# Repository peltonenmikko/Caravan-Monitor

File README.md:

# Caravan-Monitor
For monitoring caravan stuff

This is an STM32 powered monitoring station for different kinds of sensors made with caravans in mind.
It is powered by 12v car batteries. All other are off the board and connected with wires.

It shows the values on a cheap I²C OLED display and there is one button to browse the values.

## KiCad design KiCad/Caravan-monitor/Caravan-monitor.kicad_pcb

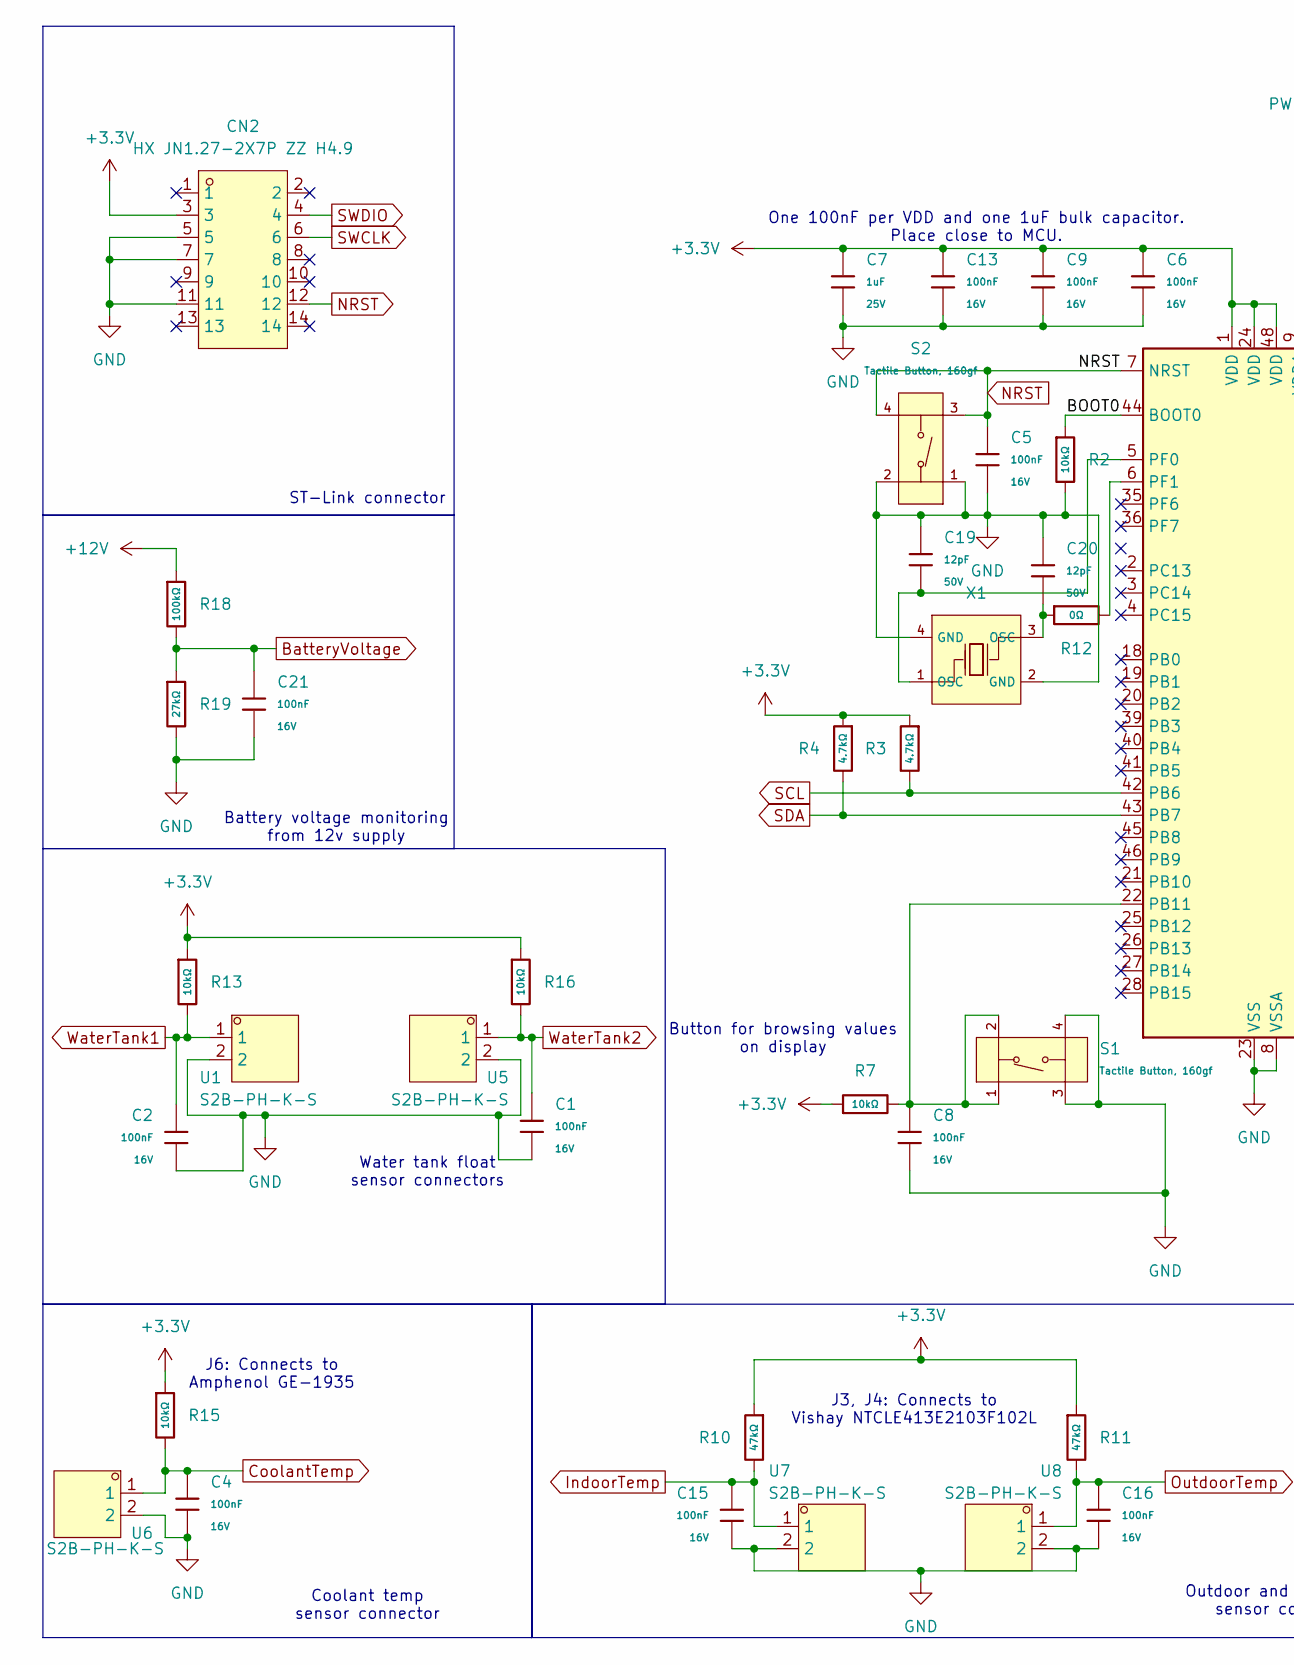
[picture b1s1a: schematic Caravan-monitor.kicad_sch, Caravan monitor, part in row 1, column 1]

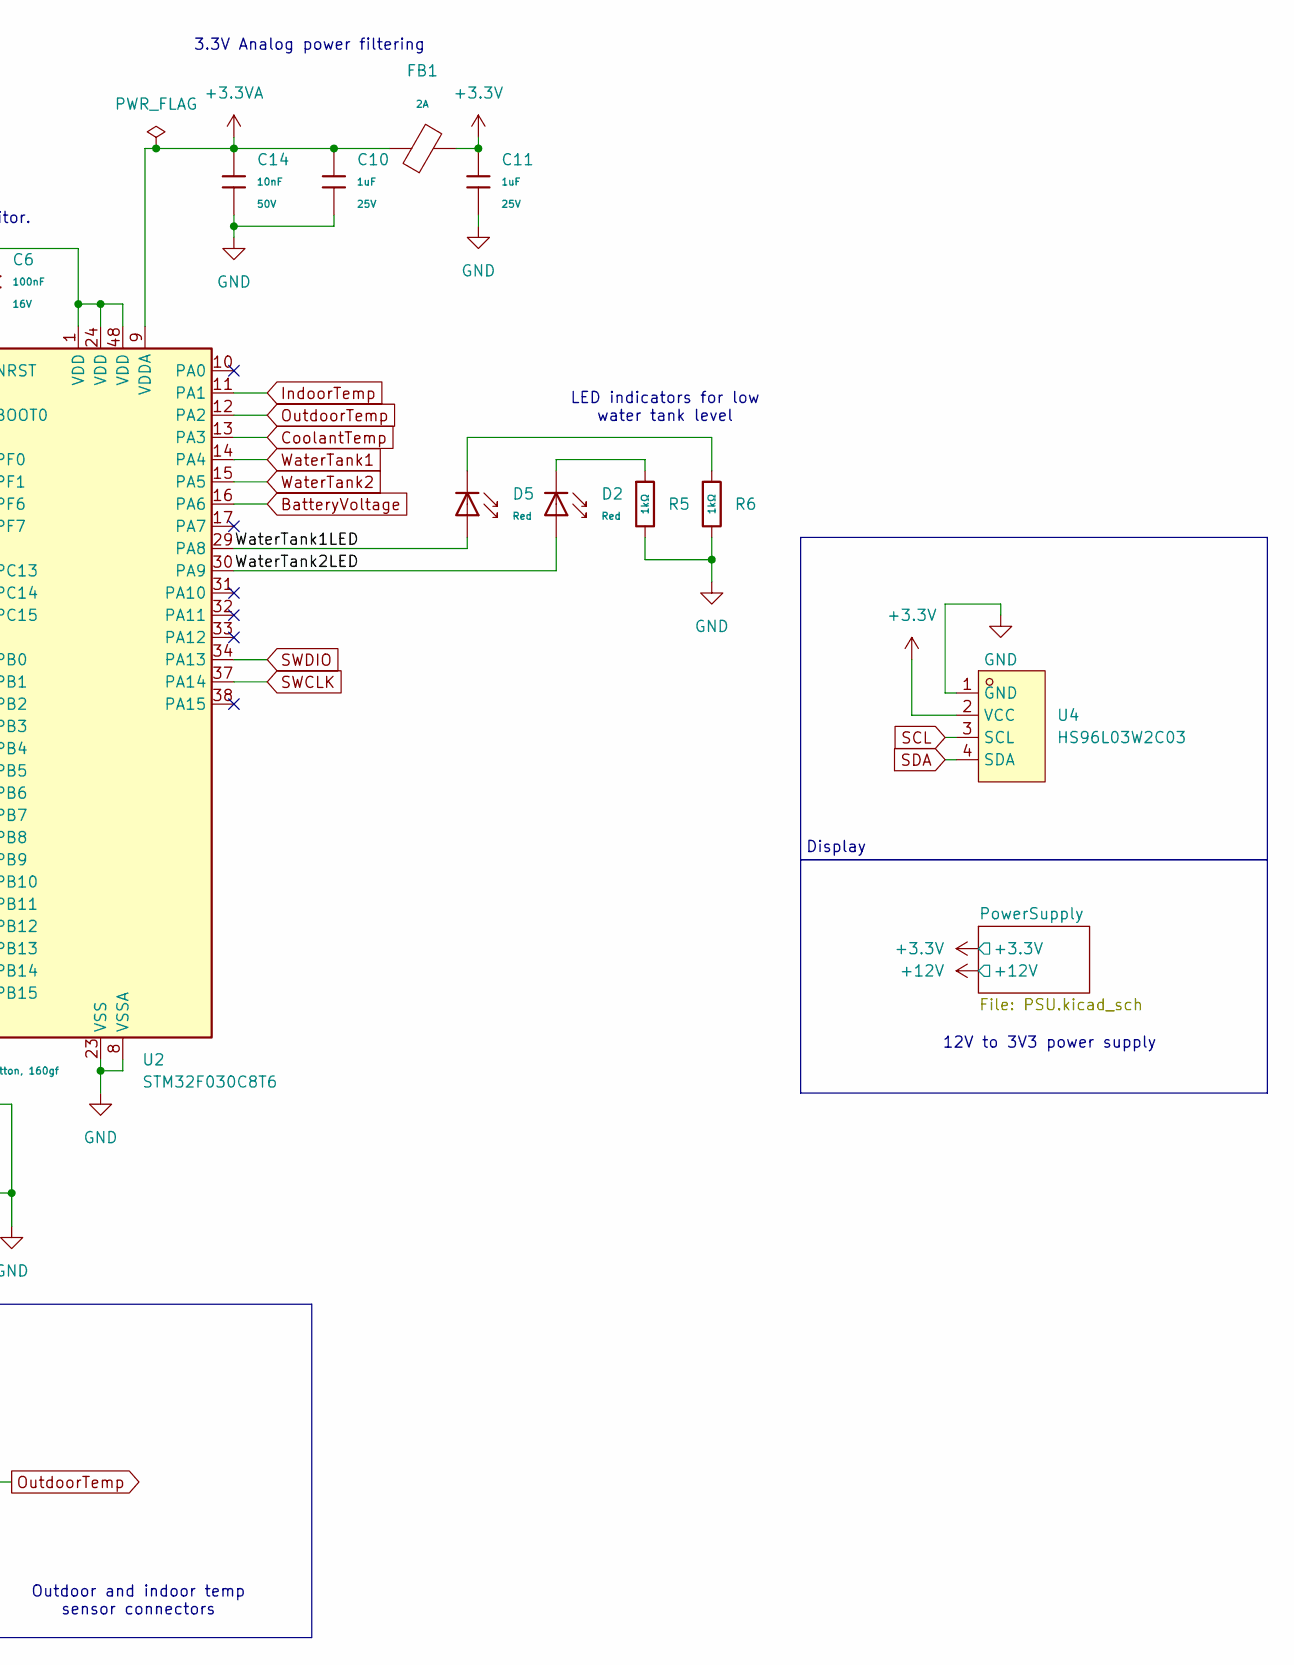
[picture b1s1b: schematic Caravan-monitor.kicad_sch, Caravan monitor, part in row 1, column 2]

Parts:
C1, C2, C4, C5, C6, C8, C9, C13, C15, C16, C21: 100nF; C_0402; Voltage Rated 16V; Tolerance ±10%; Part CL05B104KO5NNNC; LCSC C1525
C7, C10, C11: 1uF; C_0402; Voltage Rated 25V; Tolerance ±10%; Part CL05A105KA5NQNC; LCSC C52923
C14: 10nF; C_0402; Voltage Rated 50V; Tolerance ±10%; Part CL05B103KB5NNNC; LCSC C15195
C19, C20: 12pF; C_0402; Voltage Rated 50V; Tolerance ±5%; Part 0402CG120J500NT; LCSC C1547
CN2: HX JN1.27-2X7P ZZ H4.9; IDC-TH_14P-P1.27_C42455940; MPN HX JN1.27-2x7P ZZ H4.9; LCSC Part C42455940
D2, D5: Red; D_0603; Part KT-0603R; LCSC C2286
FB1: FB_0603; Current Rating 2A; Tolerance ±25%; Part BLM18PG121SN1D; LCSC C14709
R2, R7, R13, R15, R16: 10kΩ; R_0402; Overload Voltage (Max) 50V; Tolerance ±1%; Part 0402WGF1002TCE; LCSC C25744
R3, R4: 4.7kΩ; R_0402; Overload Voltage (Max) 50V; Tolerance ±1%; Part 0402WGF4701TCE; LCSC C25900
R5, R6: 1kΩ; R_0402; Overload Voltage (Max) 50V; Tolerance ±1%; Part 0402WGF1001TCE; LCSC C11702
R10, R11: 47kΩ; R_0402; Overload Voltage (Max) 50V; Tolerance ±1%; Part 0402WGF4702TCE; LCSC C25792
R12: 0Ω; R_0402; Overload Voltage (Max) 50V; Tolerance ±1%; Part 0402WGF0000TCE; LCSC C17168
R18: 100kΩ; R_0402; Overload Voltage (Max) 50V; Tolerance ±1%; Part 0402WGF1003TCE; LCSC C25741
R19: 27kΩ; R_0402; Overload Voltage (Max) 50V; Tolerance ±1%; Part 0402WGF2702TCE; LCSC C25771
S1, S2: Tactile Button, 160gf; SW-SMD_4P-L5.1-W5.1-P3.70-LS6.5-TL-2; Voltage Rating (Dc) 12V; Part TS-1187A-B-A-B; LCSC C318884
U1, U5, U6, U7, U8: S2B-PH-K-S; CONN-TH_S2B-PH-K-S-LF-SN; MPN S2B-PH-K-S(LF)(SN); LCSC Part C173752
U2: STM32F030C8T6; LQFP-48_7x7mm_P0.5mm; Operating Voltage Range 2.4V~3.6V; Low Voltage Detection T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 2.4V~3.6V; Part STM32F030C8T6; LCSC C23922
U4: HS96L03W2C03; OLED-TH_L27.8-W27.2-P2.54_C9900033791; MPN HS96L03W2C03; LCSC Part C5248080
X1: X322516MLB4SI; OSC-SMD_4P-L3.2-W2.5-BL; Frequency Tolerance ±10ppm; Part X322516MLB4SI; LCSC C13738

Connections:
+3.3V: C6.1, C7.1, C9.1, C11.1, C13.1, CN2.3, FB1.2, R3.1, R4.1, R7.1, R10.1, R11.1, R13.1, R15.1, R16.1, U2.1 (VDD), U2.24 (VDD), U2.48 (VDD), U4.2 (VCC); also elsewhere on the board
+3.3VA: C10.1, C14.1, FB1.1, U2.9 (VDDA)
+12V: R18.1; also elsewhere on the board
/BOOT0: R2.1, U2.44 (BOOT0)
/WaterTank1LED: D5.2, U2.29 (PA8)
/WaterTank2LED: D2.2, U2.30 (PA9)
BatteryVoltage: C21.1, R18.2, R19.1, U2.16 (PA6)
CoolantTemp: C4.1, R15.2, U2.13 (PA3), U6.1
GND: C1.2, C2.2, C4.2, C5.2, C6.2, C7.2, C8.2, C9.2, C10.2, C11.2, C13.2, C14.2, C15.2, C16.2, C19.1, C20.1, C21.2, CN2.5, CN2.7, CN2.11, R2.2, R5.2, R6.2, R19.2, S1.3 (C), S1.4 (D), S2.1 (A), S2.2 (B), U1.2, U2.8 (VSSA), U2.23 (VSS), U2.47 (VSS), U4.1 (GND), U5.2, U6.2, U7.2, U8.2, X1.2 (GND), X1.4 (GND); also elsewhere on the board
IndoorTemp: C15.1, R10.2, U2.11 (PA1), U7.1
NRST: C5.1, CN2.12, S2.3 (C), S2.4 (D), U2.7 (NRST)
unnamed: C20.2, R12.1, X1.3 (OSC)
unnamed: D2.1, R5.1
unnamed: D5.1, R6.1
unnamed: C8.1, R7.2, S1.1 (A), S1.2 (B), U2.22 (PB11)
unnamed: C19.2, U2.5 (PF0), X1.1 (OSC)
unnamed: R12.2, U2.6 (PF1)
OutdoorTemp: C16.1, R11.2, U2.12 (PA2), U8.1
SCL: R3.2, U2.42 (PB6), U4.3 (SCL)
SDA: R4.2, U2.43 (PB7), U4.4 (SDA)
SWCLK: CN2.6, U2.37 (PA14)
SWDIO: CN2.4, U2.34 (PA13)
WaterTank1: C2.1, R13.2, U1.1, U2.14 (PA4)
WaterTank2: C1.1, R16.2, U2.15 (PA5), U5.1

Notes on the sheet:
One 100nF per VDD and one 1uF bulk capacitor. Place close to MCU.
Display
Water tank float sensor connectors
J6: Connects to Amphenol GE-1935
Battery voltage monitoring from 12v supply
Button for browsing values on display
3.3V Analog power filtering
Outdoor and indoor temp sensor connectors
LED indicators for low water tank level
Coolant temp sensor connector
12V to 3V3 power supply
ST-Link connector
J3, J4: Connects to Vishay NTCLE413E2103F102L

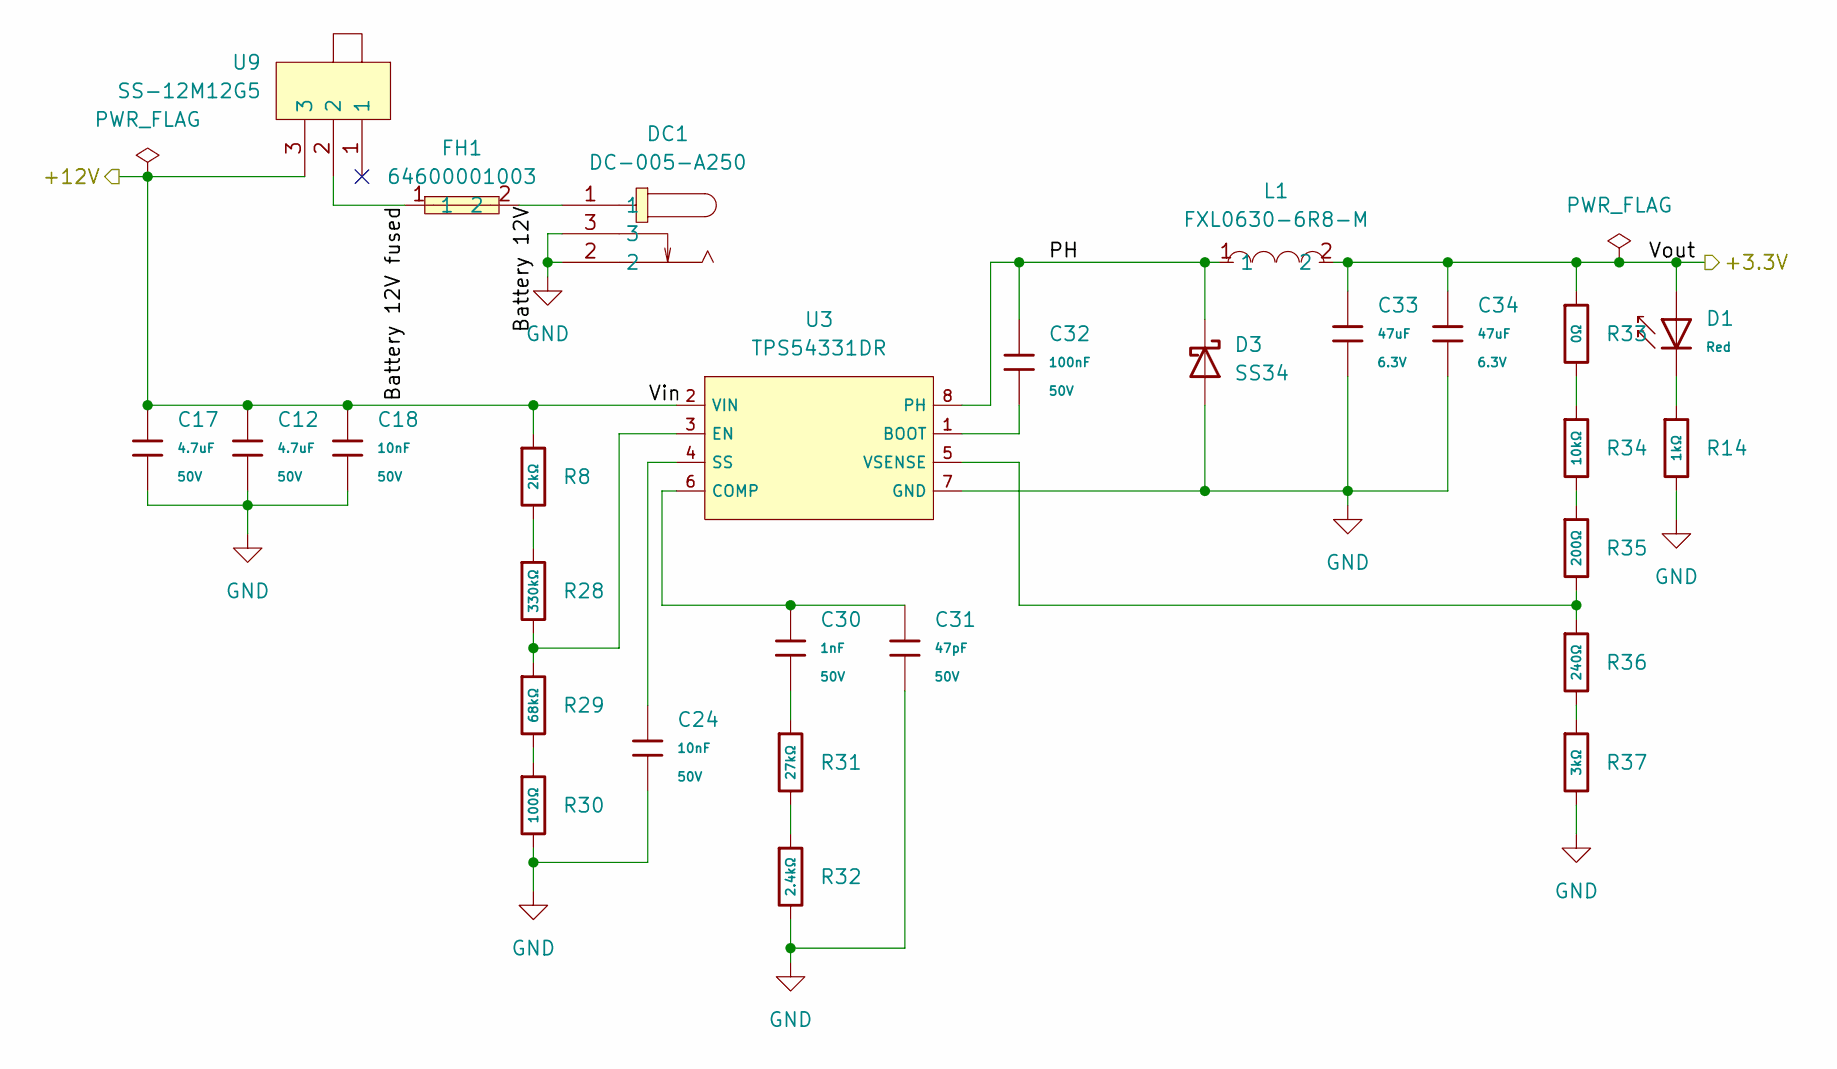
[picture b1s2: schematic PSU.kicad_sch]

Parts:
C12, C17: 4.7uF; C_1206; Voltage Rated 50V; Tolerance ±10%; Part 1206B475K500NT; LCSC C29823
C18: 10nF; C_1206; Voltage Rated 50V; Tolerance ±10%; Part 1206B103K500NT; LCSC C1846
C24: 10nF; C_0402; Voltage Rated 50V; Tolerance ±10%; Part CL05B103KB5NNNC; LCSC C15195
C30: 1nF; C_0402; Voltage Rated 50V; Tolerance ±10%; Part 0402B102K500NT; LCSC C1523
C31: 47pF; C_0402; Voltage Rated 50V; Tolerance ±5%; Part 0402CG470J500NT; LCSC C1567
C32: 100nF; C_0805; Voltage Rated 50V; Tolerance ±10%; Part CC0805KRX7R9BB104; LCSC C49678
C33, C34: 47uF; C_0805; Voltage Rated 6.3V; Tolerance ±20%; Part CL21A476MQYNNNE; LCSC C16780
D1: Red; D_0805; Forward Voltage (VF) 1.6V~2.6V; Part NCD0805R1; LCSC C84256
D3: SS34; D_SMA
DC1: DC-005-A250; DC-IN-TH_DC-005-A250; MPN DC-005-A250; LCSC Part C720558
FH1: 64600001003; MPN 64600001003; LCSC Part C206887
L1: FXL0630-6R8-M; IND-SMD_L7.0-W6.6; MPN FXL0630-6R8-M; LCSC Part C167221
R8: 2kΩ; R_0805; Overload Voltage (Max) 150V; Tolerance ±1%; Part 0805W8F2001T5E; LCSC C17604
R14: 1kΩ; R_0402; Overload Voltage (Max) 50V; Tolerance ±1%; Part 0402WGF1001TCE; LCSC C11702
R28: 330kΩ; R_0805; Overload Voltage (Max) 150V; Tolerance ±1%; Part 0805W8F3303T5E; LCSC C17629
R29: 68kΩ; R_0805; Overload Voltage (Max) 150V; Tolerance ±1%; Part 0805W8F6802T5E; LCSC C17801
R30: 100Ω; R_0805; Overload Voltage (Max) 150V; Tolerance ±1%; Part 0805W8F1000T5E; LCSC C17408
R31: 27kΩ; R_0805; Overload Voltage (Max) 150V; Tolerance ±1%; Part 0805W8F2702T5E; LCSC C17593
R32: 2.4kΩ; R_0805; Overload Voltage (Max) 150V; Tolerance ±1%; Part 0805W8F2401T5E; LCSC C17526
R33: 0Ω; R_0805; Overload Voltage (Max) 150V; Tolerance ±1%; Part 0805W8F0000T5E; LCSC C17477
R34: 10kΩ; R_0805; Overload Voltage (Max) 150V; Tolerance ±1%; Part 0805W8F1002T5E; LCSC C17414
R35: 200Ω; R_0805; Overload Voltage (Max) 150V; Tolerance ±1%; Part 0805W8F2000T5E; LCSC C17540
R36: 240Ω; R_0805; Overload Voltage (Max) 150V; Tolerance ±1%; Part 0805W8F2400T5E; LCSC C17572
R37: 3kΩ; R_0805; Overload Voltage (Max) 150V; Tolerance ±1%; Part 0805W8F3001T5E; LCSC C17661
U3: TPS54331DR; SOIC-8_L5.0-W4.0-P1.27-LS6.0-BL; Output Voltage 0.8V~25V; Input Voltage 3.5V~28V; Part TPS54331DR; LCSC C9865
U9: SS-12M12G5; SW-TH_SS-12M12G5; MPN SS-12M12G5; LCSC Part C2884789

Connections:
+3.3V: C33.1, C34.1, D1.2, L1.2, R33.1; also elsewhere on the board
+12V: C12.1, C17.1, C18.1, R8.1, U3.2 (VIN), U9.3; also elsewhere on the board
/PowerSupply/Battery 12V: DC1.1, FH1.2
/PowerSupply/Battery 12V fused: FH1.1, U9.2
/PowerSupply/PH: C32.1, D3.1 (K), L1.1, U3.8 (PH)
GND: C12.2, C17.2, C18.2, C24.2, C31.2, C33.2, C34.2, D3.2 (A), DC1.2, DC1.3, R14.2, R30.2, R32.2, R37.2, U3.7 (GND); also elsewhere on the board
unnamed: C30.2, R31.1
unnamed: D1.1, R14.1
unnamed: R8.2, R28.1
unnamed: R29.2, R30.1
unnamed: R31.2, R32.1
unnamed: R33.2, R34.1
unnamed: R34.2, R35.1
unnamed: R36.2, R37.1
unnamed: C32.2, U3.1 (BOOT)
unnamed: C30.1, C31.1, U3.6 (COMP)
unnamed: R28.2, R29.1, U3.3 (EN)
unnamed: C24.1, U3.4 (SS)
unnamed: R35.2, R36.1, U3.5 (VSENSE)

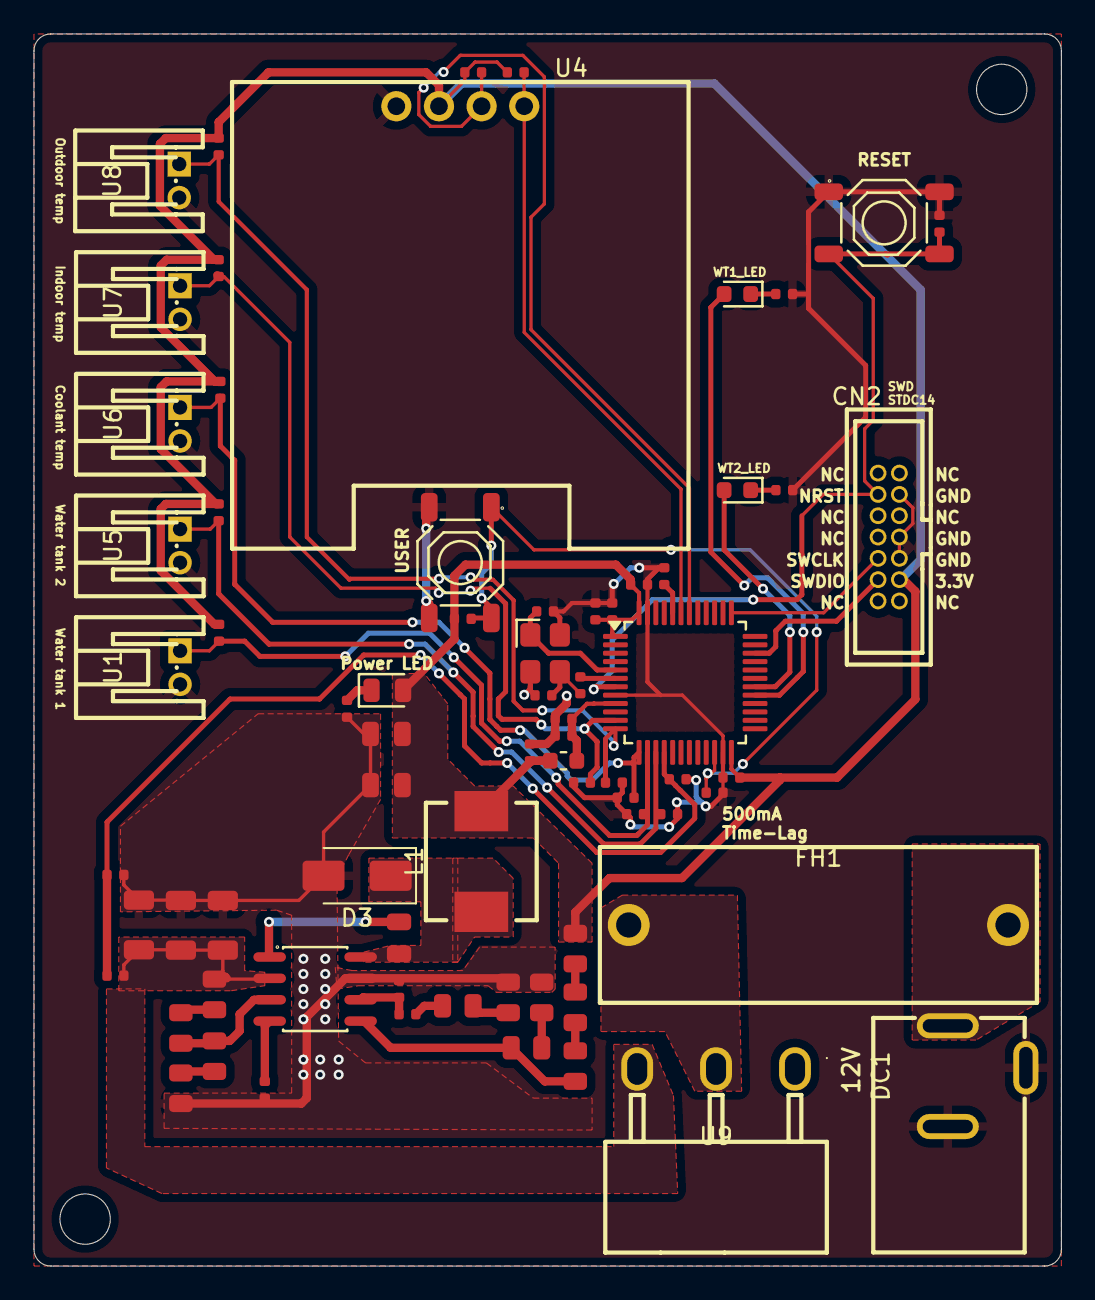
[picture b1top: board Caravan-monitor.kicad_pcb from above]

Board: 2 copper layers, 61.2 x 73.4 mm, 73 parts (0 on the bottom side), 40 nets.

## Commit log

2026-05-10 Create KiCad and LTSpice folders
2026-05-10 PSU schematic done
2026-05-10 Battery voltage monitoring schematics
2026-05-10 Temperature monitoring schematics
2026-05-10 Coolant temoerature measurement
2026-05-10 Display schematics
2026-05-11 Schematics done
2026-05-11 3.3V and 5V PSU layout done
2026-05-11 PCB Designed
2026-05-11 Version 0.1 complete
2026-05-11 Add image of PCB
2026-05-11 Update README
    brief description and an image of pcb
2026-05-12 test v0.2 branch commit
2026-05-12 Schematic updates
    Parts changed for JLCPCB assembly compatibility
2026-05-12 12V to 3.3V converter done
2026-05-13 V0.2 PCB complete
2026-05-13 Updated README with image of new PCB
2026-05-14 Updated README
    fixed a typo
